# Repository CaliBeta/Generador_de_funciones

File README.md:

# Generador_de_funciones
Generador de señales analógicas seno, triangular y cuadrada. control de amplitud, frecuencia y offset 

Revisar el archivo PDF adjunto en el repositorio, en el se encuentran los calculos realizados en el proceso de diseño

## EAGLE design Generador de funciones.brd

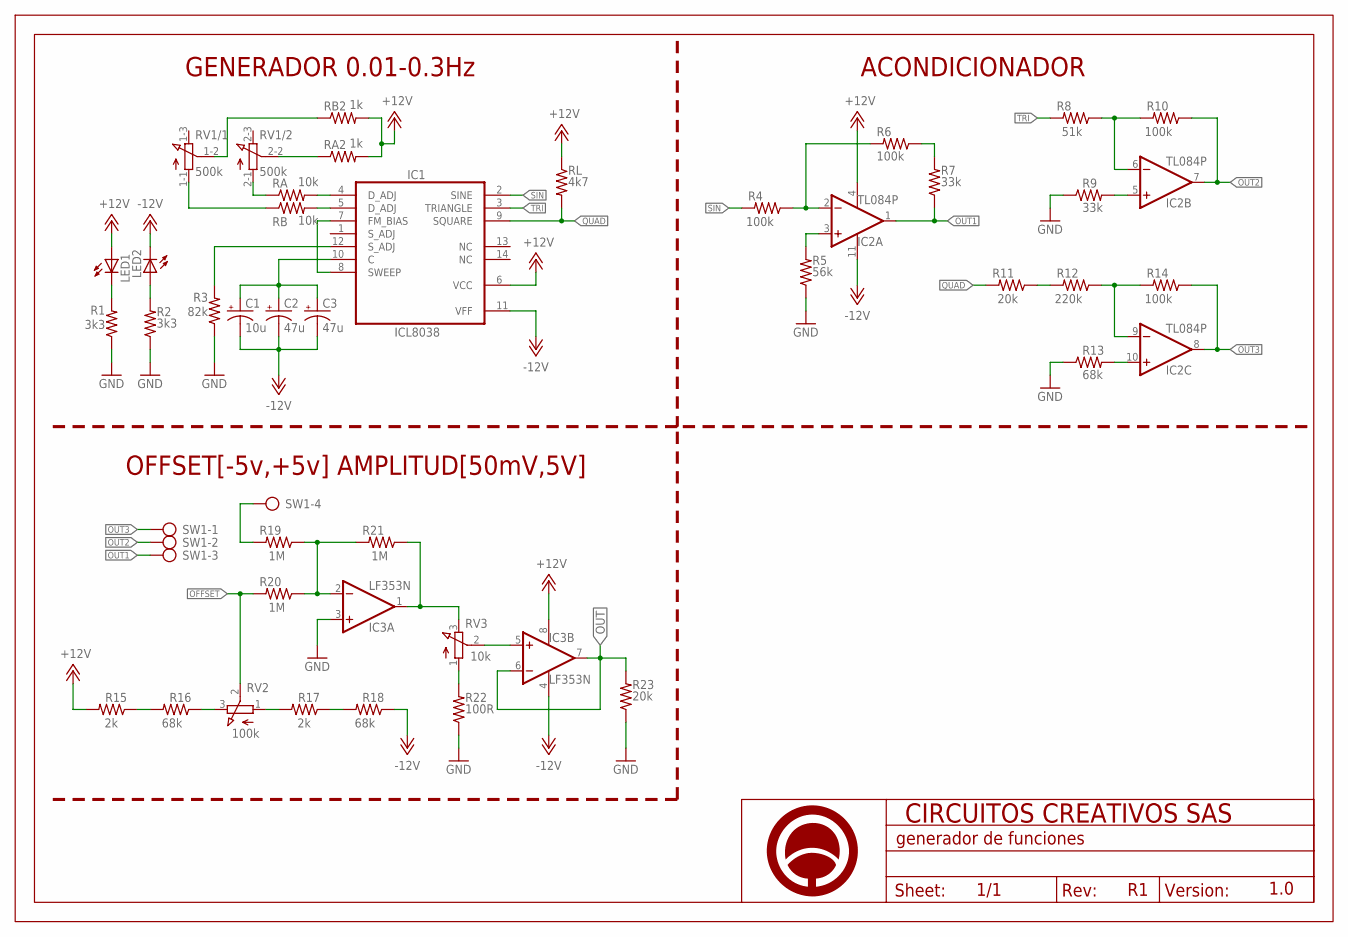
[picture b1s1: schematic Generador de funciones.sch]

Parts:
C1: 10u; E2-5
C2, C3: 47u; E2-5
FRAME1: A4_HORIZONTAL; LOGO
IC1: ICL8038; DIL14
IC2: TL084P; DIL14
IC3: LF353N; DIL08
LED1, LED2: LED3MM
R1, R2: 3k3; 0204/7
R3: 82k; 0204/7
R4, R6, R10, R14: 100k; 0204/7
R5: 56k; 0204/7
R7, R9: 33k; 0204/7
R8: 51k; 0204/7
R11, R23: 20k; 0204/7
R12: 220k; 0204/7
R13, R16, R18: 68k; 0204/7
R15, R17: 2k; 0204/7
R19, R20, R21: 1M; 0204/7
R22: 100R; 0204/7
RA: 10k; 0204/7
RA2: 1k; 0204/7
RB: 10k; 0204/7
RB2: 1k; 0204/7
RL: 4k7; 0204/7
RV1: 500k; 3RP/1610G
RV2: 100k; 3RP/1610N
RV3: 10k; 3RP/1610N
SW1: AK500/4

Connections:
+12V: IC1.6 (VCC), IC2.4 (V+), IC3.8 (V+), LED1.A, R15.2, RA2.2, RB2.2, RL.1
-12V: C1.-, C2.-, C3.-, IC1.11 (VFF), IC2.11 (V-), IC3.4 (V-), LED2.K (C), R18.1
GND: IC3.3 (+IN), R1.1, R2.1, R3.1, R5.1, R9.1, R13.1, R22.1, R23.1
unnamed: IC1.7 (FM_BIAS), IC1.8 (SWEEP)
unnamed: C1.+, C2.+, C3.+, IC1.10 (C)
unnamed: IC1.12 (S_ADJ), R3.2
unnamed: IC1.4 (D_ADJ), RA.2
unnamed: IC1.5 (D_ADJ), RB.2
unnamed: RA.1, RV1.2-1 (A)
unnamed: RB2.1, RV1.1-2 (S)
unnamed: RB.1, RV1.1-1 (A)
unnamed: RA2.1, RV1.2-2 (S)
unnamed: LED1.K (C), R1.2
unnamed: LED2.A, R2.2
unnamed: IC2.3 (+IN), R5.2
unnamed: IC2.2 (-IN), R4.1, R6.2
unnamed: IC2.9 (-IN), R12.1, R14.2
unnamed: R6.1, R7.2
unnamed: IC2.6 (-IN), R8.1, R10.2
unnamed: IC2.5 (+IN), R9.2
unnamed: IC2.10 (+IN), R13.2
unnamed: R11.1, R12.2
unnamed: R19.2, SW1.4
unnamed: IC3.1 (OUT), R21.1, RV3.3 (E)
unnamed: IC3.2 (-IN), R19.1, R20.1, R21.2
unnamed: R15.1, R16.2
unnamed: R16.1, RV2.3 (E)
unnamed: R17.2, RV2.1 (A)
unnamed: R17.1, R18.2
unnamed: IC3.5 (+IN), RV3.2 (S)
unnamed: R22.2, RV3.1 (A)
OFFSET: R20.2, RV2.2 (S)
OUT: IC3.6 (-IN), IC3.7 (OUT), R23.2
OUT1: IC2.1 (OUT), R7.1, SW1.3
OUT2: IC2.7 (OUT), R10.1, SW1.2
OUT3: IC2.8 (OUT), R14.1, SW1.1
QUAD: IC1.9 (SQUARE), R11.2, RL.2
SIN: IC1.2 (SINE), R4.2
TRI: IC1.3 (TRIANGLE), R8.2

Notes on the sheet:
GENERADOR 0.01-0.3Hz
ACONDICIONADOR
OFFSET[-5v,+5v] AMPLITUD[50mV,5V]
1.0

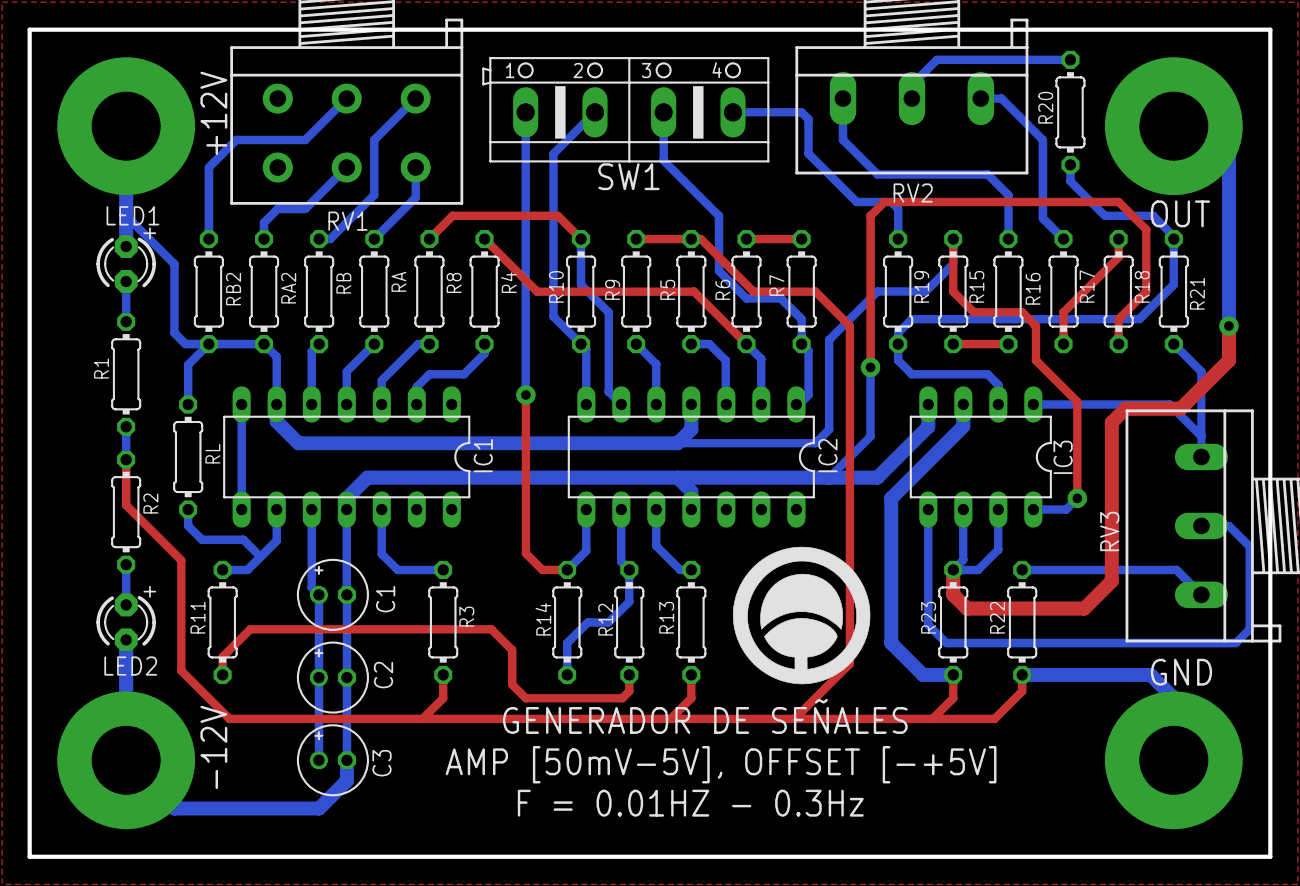
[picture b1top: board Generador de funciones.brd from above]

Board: 2 copper layers, 90.0 x 60.0 mm, 41 parts (0 on the bottom side), 39 nets.

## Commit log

2017-08-14 Commit inicial, Casi completo el SCH
2017-09-19 Terminado SCH. Andersson Inicia BRD
2017-09-28 BRD de Andersson con errores. Inicio mi propio BRD
2017-09-28 Terminado Ubicacion de componentes. Inicio del ruteo
2017-09-28 Ruteo al 50%. Se esta realizando a doble capa
2017-09-28 Liberado version 1.0
2019-01-15 Generado imagenes SCH y BRD
2019-01-15 Agregado PDF con los cálculos del diseño
